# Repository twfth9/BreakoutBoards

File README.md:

# BreakoutBoards
Collection of PCB breakout boards

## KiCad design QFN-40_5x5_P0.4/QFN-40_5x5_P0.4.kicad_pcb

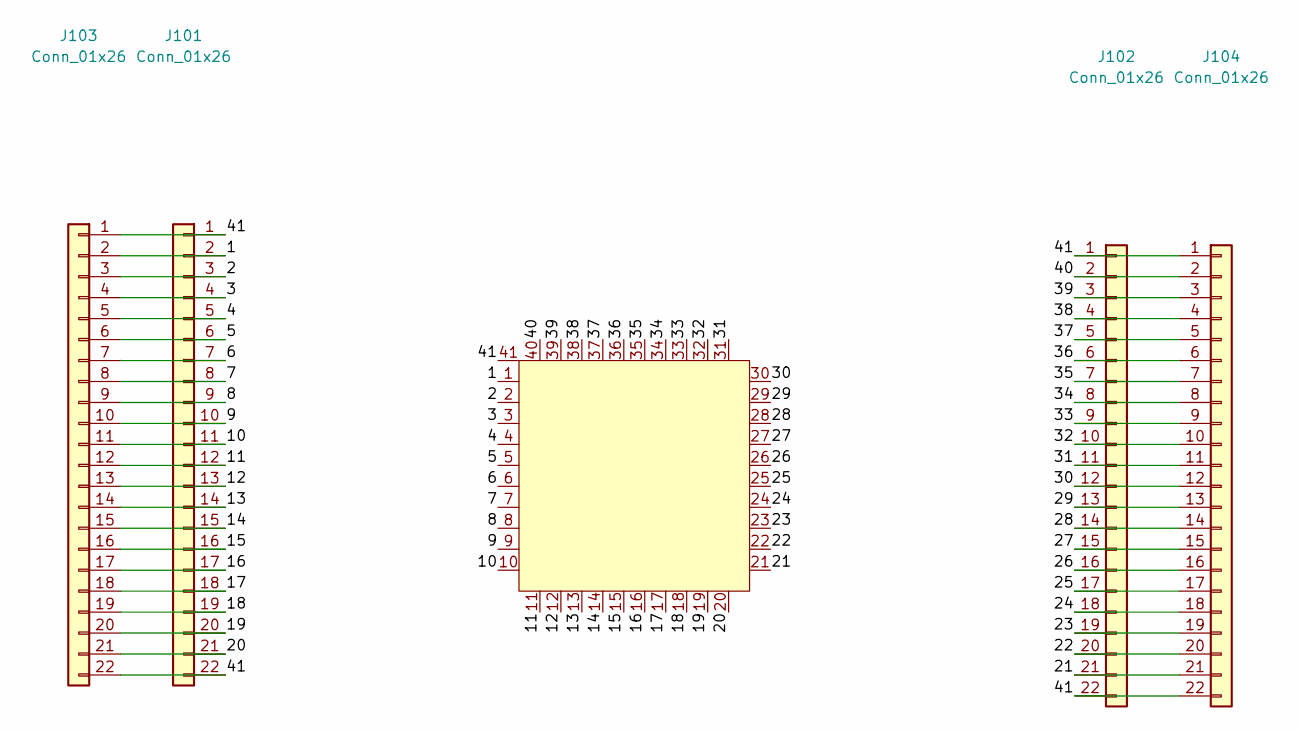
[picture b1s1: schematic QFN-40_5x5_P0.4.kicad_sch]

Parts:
J101, J102: Conn_01x26; PinHeader_1x22_P2.54mm_Vertical
J103: Conn_01x26; PinHeader_1x22_P2.54mm_Vertical_SMD_Pin1Left
J104: Conn_01x26; PinHeader_1x22_P2.54mm_Vertical_SMD_Pin1Right
U101: QFN-48; QFN-40-1EP_5x5mm_P0.4mm_EP3.6x3.6mm_ThermalVias

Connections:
/1: J101.2, J103.2, U101.1
/2: J101.3, J103.3, U101.2
/3: J101.4, J103.4, U101.3
/4: J101.5, J103.5, U101.4
/5: J101.6, J103.6, U101.5
/6: J101.7, J103.7, U101.6
/7: J101.8, J103.8, U101.7
/8: J101.9, J103.9, U101.8
/9: J101.10, J103.10, U101.9
/10: J101.11, J103.11, U101.10
/11: J101.12, J103.12, U101.11
/12: J101.13, J103.13, U101.12
/13: J101.14, J103.14, U101.13
/14: J101.15, J103.15, U101.14
/15: J101.16, J103.16, U101.15
/16: J101.17, J103.17, U101.16
/17: J101.18, J103.18, U101.17
/18: J101.19, J103.19, U101.18
/19: J101.20, J103.20, U101.19
/20: J101.21, J103.21, U101.20
/21: J102.21, J104.21, U101.21
/22: J102.20, J104.20, U101.22
/23: J102.19, J104.19, U101.23
/24: J102.18, J104.18, U101.24
/25: J102.17, J104.17, U101.25
/26: J102.16, J104.16, U101.26
/27: J102.15, J104.15, U101.27
/28: J102.14, J104.14, U101.28
/29: J102.13, J104.13, U101.29
/30: J102.12, J104.12, U101.30
/31: J102.11, J104.11, U101.31
/32: J102.10, J104.10, U101.32
/33: J102.9, J104.9, U101.33
/34: J102.8, J104.8, U101.34
/35: J102.7, J104.7, U101.35
/36: J102.6, J104.6, U101.36
/37: J102.5, J104.5, U101.37
/38: J102.4, J104.4, U101.38
/39: J102.3, J104.3, U101.39
/40: J102.2, J104.2, U101.40
/41: J101.1, J101.22, J102.1, J102.22, J103.1, J103.22, J104.1, J104.22, U101.41

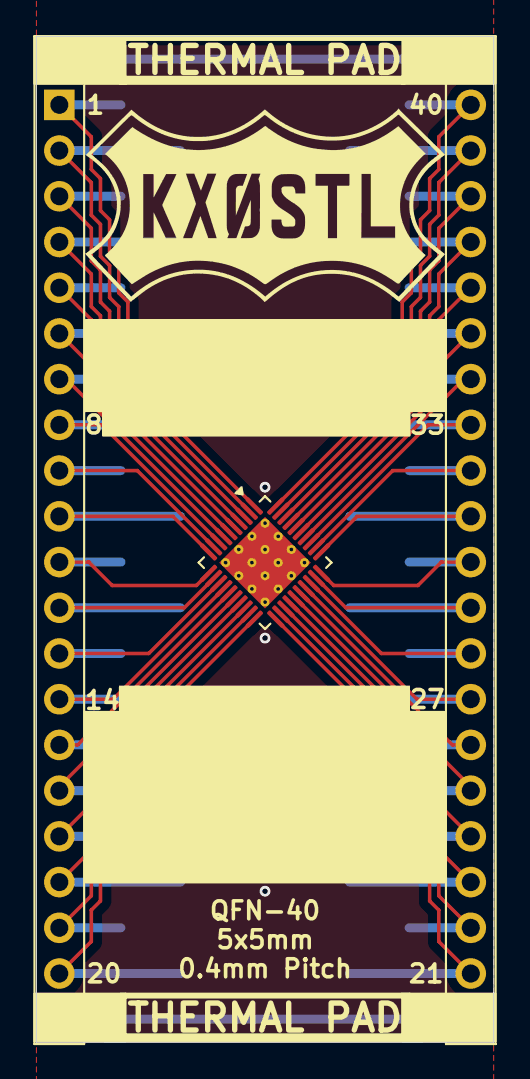
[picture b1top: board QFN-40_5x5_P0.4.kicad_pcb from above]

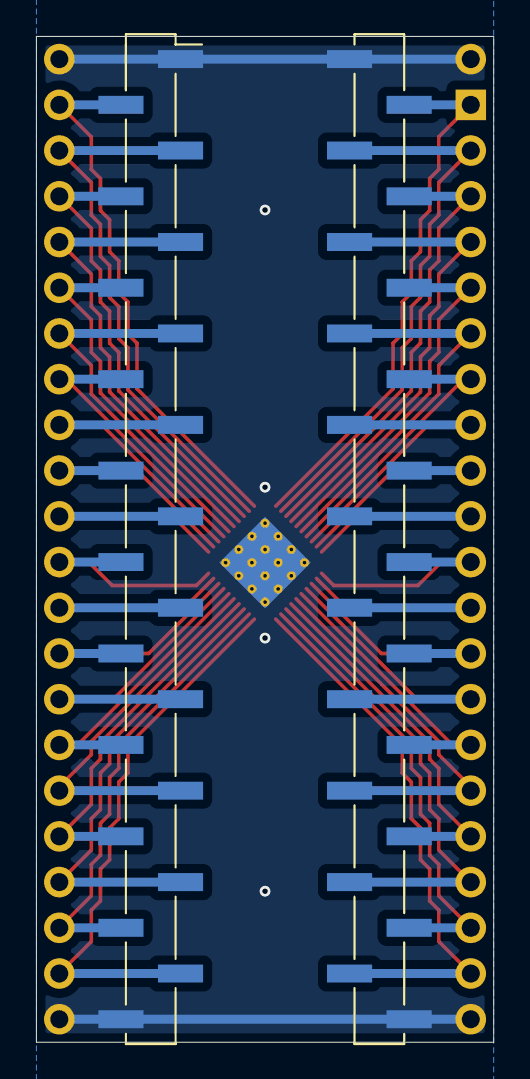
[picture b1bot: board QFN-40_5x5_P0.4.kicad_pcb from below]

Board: 2 copper layers, 25.4 x 55.9 mm, 5 parts (2 on the bottom side), 41 nets.

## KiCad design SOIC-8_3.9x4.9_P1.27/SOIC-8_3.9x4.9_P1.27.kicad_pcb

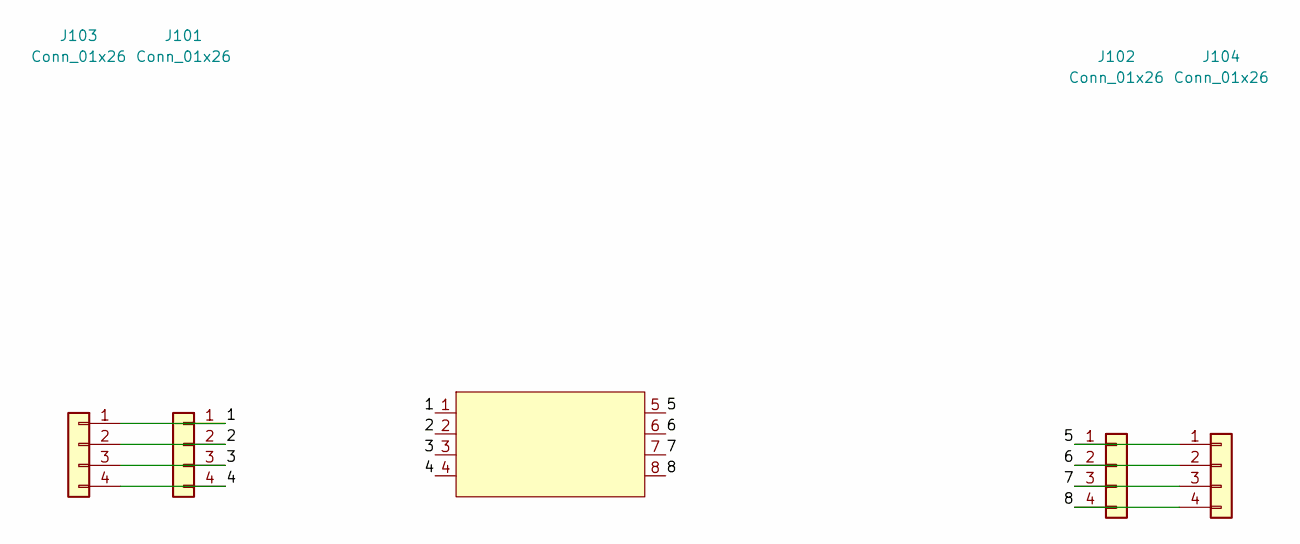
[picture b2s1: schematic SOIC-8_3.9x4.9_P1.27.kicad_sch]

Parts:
J101, J102: Conn_01x26; PinHeader_1x04_P2.54mm_Vertical
J103, J104: Conn_01x26; PinHeader_1x04_P2.54mm_Vertical_SMD_Pin1Right
U101: SOIC-8; SOIC-8_3.9x4.9mm_P1.27mm

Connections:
/1: J101.1, J103.1, U101.1
/2: J101.2, J103.2, U101.2
/3: J101.3, J103.3, U101.3
/4: J101.4, J103.4, U101.4
/5: J102.1, J104.1, U101.5
/6: J102.2, J104.2, U101.6
/7: J102.3, J104.3, U101.7
/8: J102.4, J104.4, U101.8

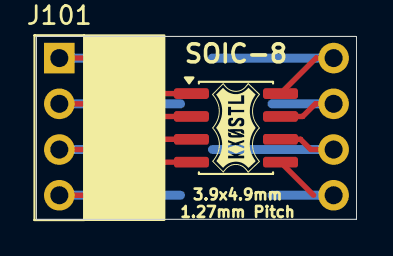
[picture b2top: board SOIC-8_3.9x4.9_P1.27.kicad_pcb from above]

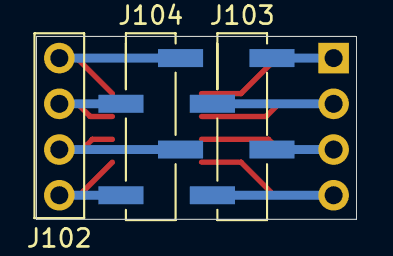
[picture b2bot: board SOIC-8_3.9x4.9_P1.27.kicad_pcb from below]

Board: 2 copper layers, 17.8 x 10.2 mm, 5 parts (3 on the bottom side), 8 nets.

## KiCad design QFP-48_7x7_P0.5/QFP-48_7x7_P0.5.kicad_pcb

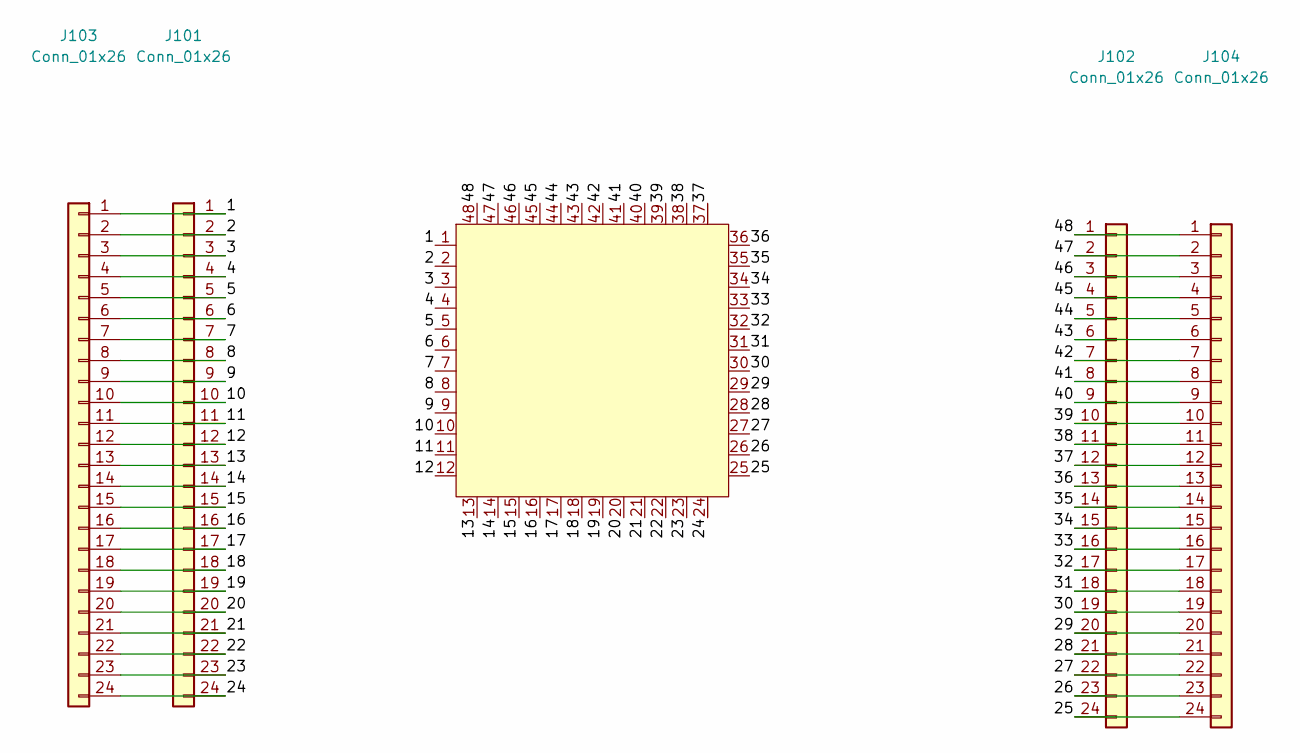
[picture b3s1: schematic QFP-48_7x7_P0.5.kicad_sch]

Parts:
J101, J102: Conn_01x26; PinHeader_1x24_P2.54mm_Vertical
J103: Conn_01x26; PinHeader_1x24_P2.54mm_Vertical_SMD_Pin1Left
J104: Conn_01x26; PinHeader_1x24_P2.54mm_Vertical_SMD_Pin1Right
U101: QFN-48; LQFP-48_7x7mm_P0.5mm

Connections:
/1: J101.1, J103.1, U101.1
/2: J101.2, J103.2, U101.2
/3: J101.3, J103.3, U101.3
/4: J101.4, J103.4, U101.4
/5: J101.5, J103.5, U101.5
/6: J101.6, J103.6, U101.6
/7: J101.7, J103.7, U101.7
/8: J101.8, J103.8, U101.8
/9: J101.9, J103.9, U101.9
/10: J101.10, J103.10, U101.10
/11: J101.11, J103.11, U101.11
/12: J101.12, J103.12, U101.12
/13: J101.13, J103.13, U101.13
/14: J101.14, J103.14, U101.14
/15: J101.15, J103.15, U101.15
/16: J101.16, J103.16, U101.16
/17: J101.17, J103.17, U101.17
/18: J101.18, J103.18, U101.18
/19: J101.19, J103.19, U101.19
/20: J101.20, J103.20, U101.20
/21: J101.21, J103.21, U101.21
/22: J101.22, J103.22, U101.22
/23: J101.23, J103.23, U101.23
/24: J101.24, J103.24, U101.24
/25: J102.24, J104.24, U101.25
/26: J102.23, J104.23, U101.26
/27: J102.22, J104.22, U101.27
/28: J102.21, J104.21, U101.28
/29: J102.20, J104.20, U101.29
/30: J102.19, J104.19, U101.30
/31: J102.18, J104.18, U101.31
/32: J102.17, J104.17, U101.32
/33: J102.16, J104.16, U101.33
/34: J102.15, J104.15, U101.34
/35: J102.14, J104.14, U101.35
/36: J102.13, J104.13, U101.36
/37: J102.12, J104.12, U101.37
/38: J102.11, J104.11, U101.38
/39: J102.10, J104.10, U101.39
/40: J102.9, J104.9, U101.40
/41: J102.8, J104.8, U101.41
/42: J102.7, J104.7, U101.42
/43: J102.6, J104.6, U101.43
/44: J102.5, J104.5, U101.44
/45: J102.4, J104.4, U101.45
/46: J102.3, J104.3, U101.46
/47: J102.2, J104.2, U101.47
/48: J102.1, J104.1, U101.48

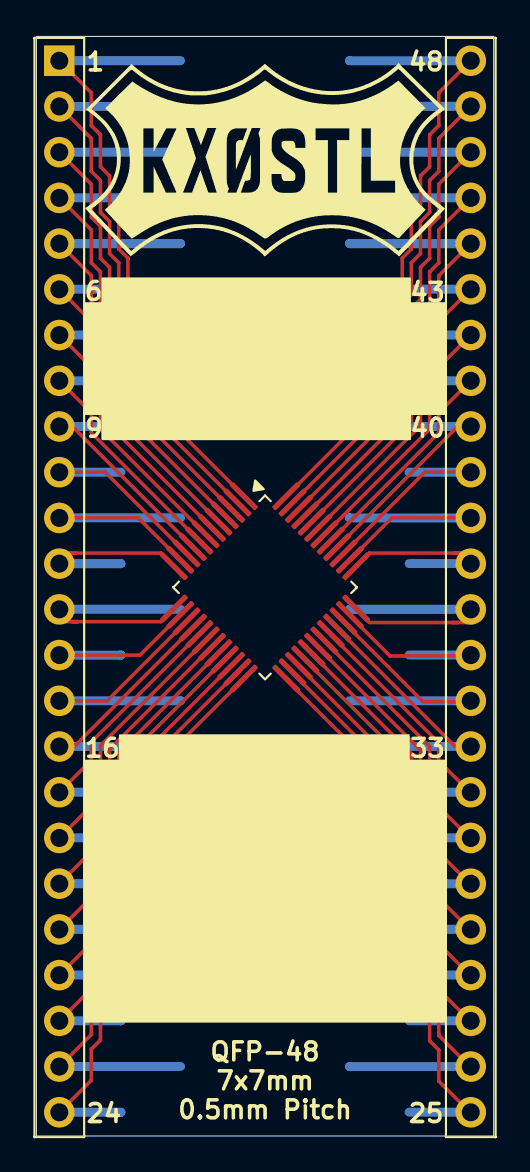
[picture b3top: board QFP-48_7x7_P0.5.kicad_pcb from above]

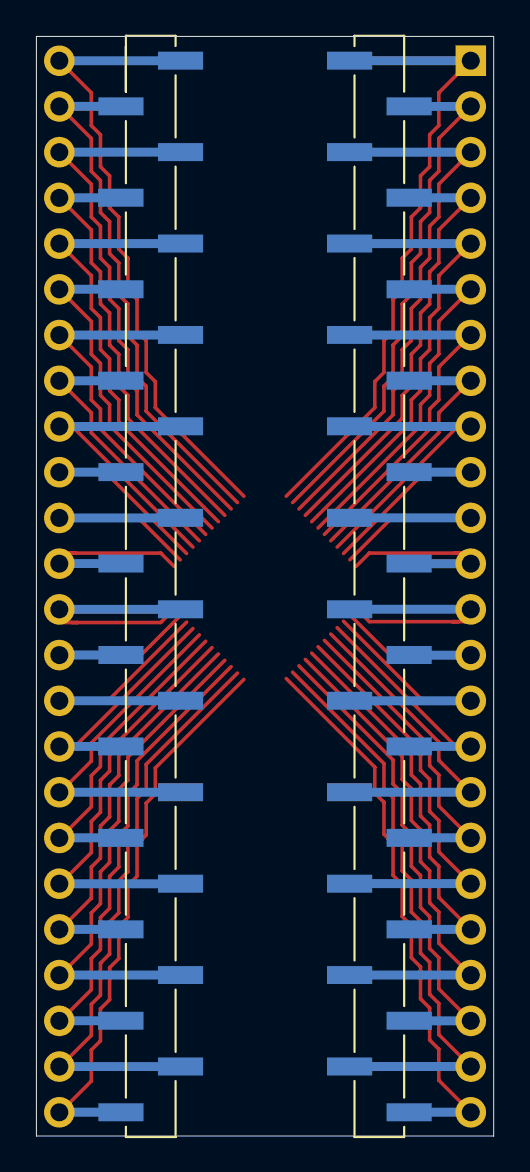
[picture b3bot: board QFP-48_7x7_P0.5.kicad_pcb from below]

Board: 2 copper layers, 25.4 x 61.1 mm, 5 parts (2 on the bottom side), 48 nets.

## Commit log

2026-01-01 QFN68, QFN48, QFN20, QFN16
2026-01-02 Created FFC-40, PiPico_BOB
2026-01-03 More boards
2026-01-05 Added SSOP-28, SOT-666, SOIC-8, SOIC-16, QFN-64
2026-01-08 Created SMDIP-16, QFP-48, QFP-32, QFN-80, QFN-68, QFN-64, QFN-60, QFN-56, QFN-48, QFN-36, QFN-28, QFN-20, QFP-32, QFP-48
2026-01-08 Fixed SOIC-8 labels
2026-01-09 Created QFN-48_7x7, QFN-48_5x5, QFN-40_5x5, QFN-24_4x4
